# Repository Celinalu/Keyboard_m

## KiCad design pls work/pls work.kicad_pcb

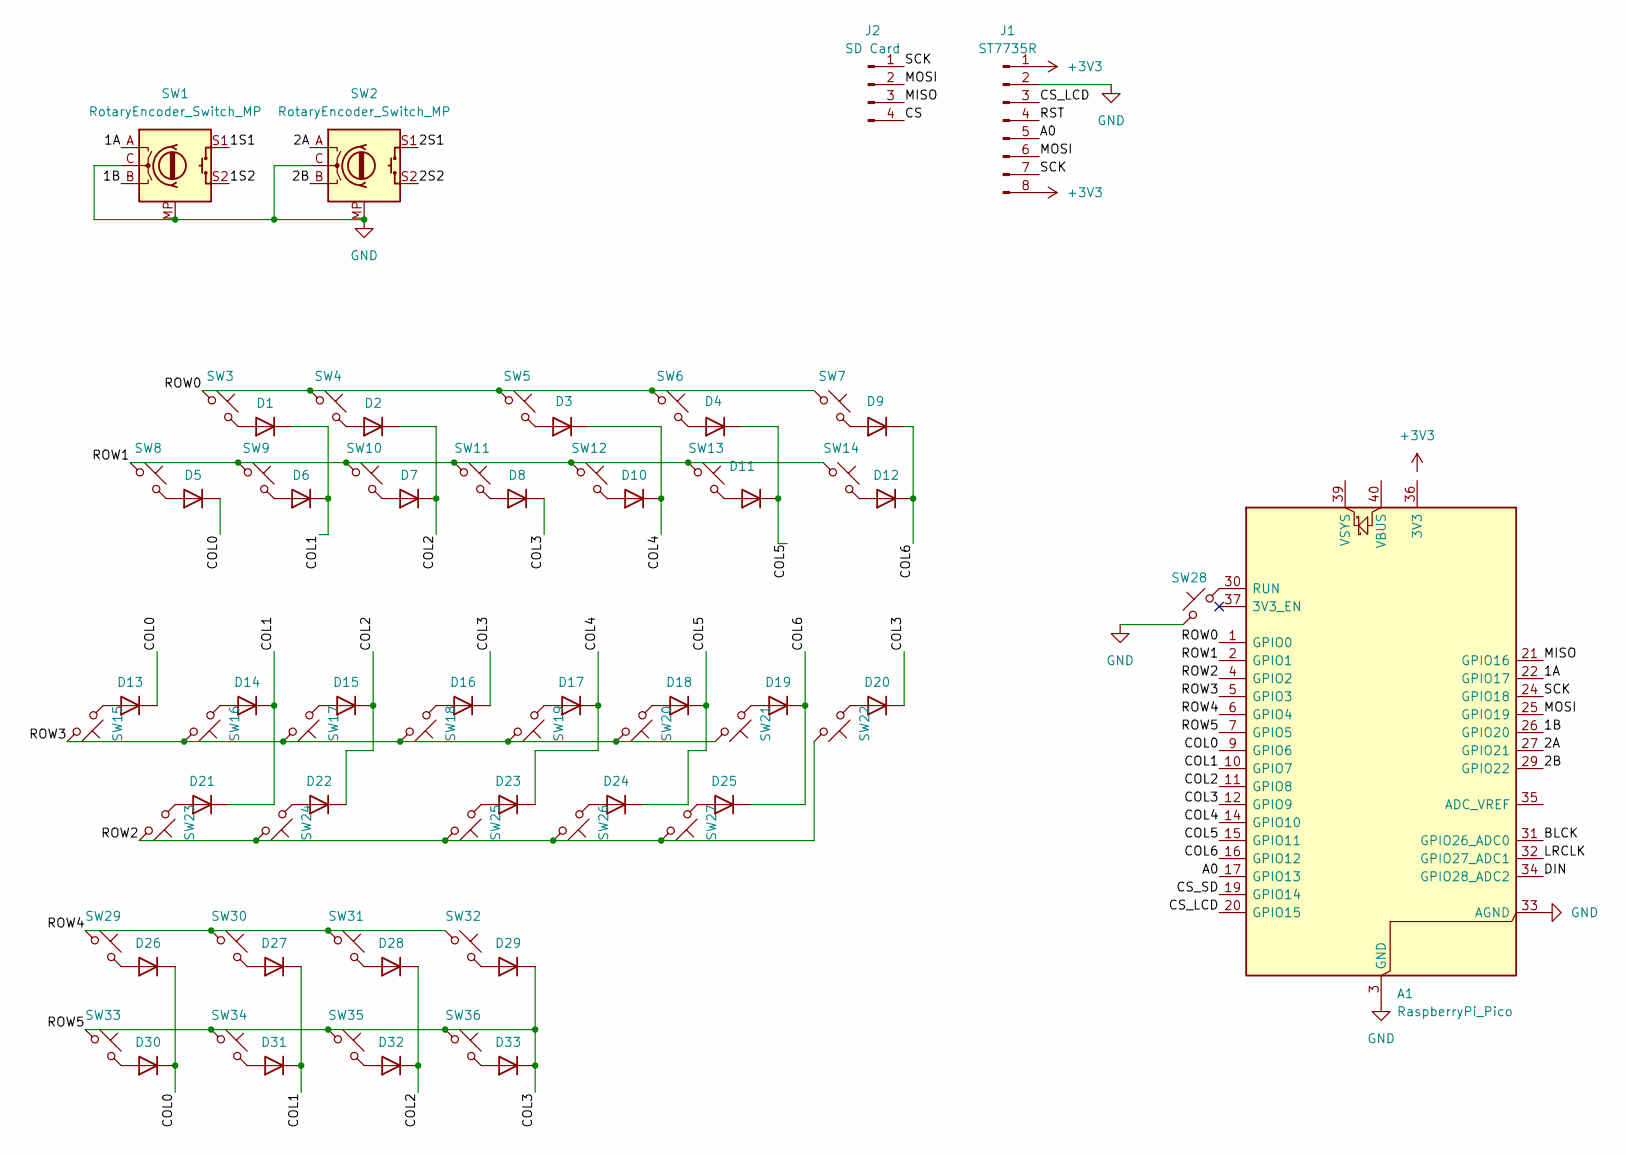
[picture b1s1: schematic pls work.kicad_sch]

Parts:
A1: RaspberryPi_Pico; RaspberryPi_Pico_Common_THT
D1, D2, D3, D4, D5, D6, D7, D8, D9, D10, D11, D12, D13, D14, D15, D16, D17, D18, D19, D20, D21, D22, D23, D24, D25, D26, D27, D28, D29, D30, D31, D32, D33: 1N4148; D_DO-35_SOD27_P7.62mm_Horizontal
J1: ST7735R; PinHeader_1x08_P1.00mm_Vertical
J2: SD Card; PinHeader_1x04_P1.00mm_Vertical
SW1, SW2: RotaryEncoder_Switch_MP; RotaryEncoder_Alps_EC11E-Switch_Vertical_H20mm_MountingHoles
SW3, SW4, SW5, SW6, SW7, SW8, SW9, SW10, SW11, SW12, SW13, SW14, SW15, SW16, SW17, SW18, SW19, SW20, SW21, SW22, SW23, SW24, SW25, SW26, SW27, SW28, SW29, SW30, SW31, SW32, SW33, SW34, SW35, SW36: SW_Push_45deg; SW_Cherry_MX_1.00u_PCB

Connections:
+3V3: J1.1, J1.8
/1A: A1.22 (GPIO17), SW1.A
/1B: A1.26 (GPIO20), SW1.B
/1S1: SW1.S1
/1S2: SW1.S2
/2A: A1.27 (GPIO21), SW2.A
/2B: A1.29 (GPIO22), SW2.B
/2S1: SW2.S1
/2S2: SW2.S2
/A0: A1.17 (GPIO13), J1.5
/BLCK: A1.31 (GPIO26_ADC0)
/COL0: A1.9 (GPIO6), D5.1 (K), D13.1 (K), D26.1 (K), D30.1 (K)
/COL1: A1.10 (GPIO7), D1.1 (K), D6.1 (K), D14.1 (K), D21.1 (K), D27.1 (K), D31.1 (K)
/COL2: A1.11 (GPIO8), D2.1 (K), D7.1 (K), D15.1 (K), D22.1 (K), D28.1 (K), D32.1 (K)
/COL3: A1.7 (GPIO5), A1.12 (GPIO9), D8.1 (K), D16.1 (K), D20.1 (K), D29.1 (K), D33.1 (K), SW33.1, SW34.1, SW35.1, SW36.1
/COL4: A1.14 (GPIO10), D3.1 (K), D10.1 (K), D17.1 (K), D23.1 (K)
/COL5: A1.15 (GPIO11), D4.1 (K), D11.1 (K), D18.1 (K), D24.1 (K)
/COL6: A1.16 (GPIO12), D9.1 (K), D12.1 (K), D19.1 (K), D25.1 (K)
/CS: J2.4
/CS_LCD: A1.20 (GPIO15), J1.3
/CS_SD: A1.19 (GPIO14)
/DIN: A1.34 (GPIO28_ADC2)
/LRCLK: A1.32 (GPIO27_ADC1)
/MISO: A1.21 (GPIO16), J2.3
/MOSI: A1.25 (GPIO19), J1.6, J2.2
/ROW0: A1.1 (GPIO0), SW3.1, SW4.1, SW5.1, SW6.1, SW7.1
/ROW1: A1.2 (GPIO1), SW8.1, SW9.1, SW10.1, SW11.1, SW12.1, SW13.1, SW14.1
/ROW2: A1.4 (GPIO2), SW22.2, SW23.2, SW24.2, SW25.2, SW26.2, SW27.2
/ROW3: A1.5 (GPIO3), SW15.2, SW16.2, SW17.2, SW18.2, SW19.2, SW20.2, SW21.2
/ROW4: A1.6 (GPIO4), SW29.1, SW30.1, SW31.1, SW32.1
/RST: J1.4
/SCK: A1.24 (GPIO18), J1.7, J2.1
GND: A1.3 (GND), A1.8 (GND), A1.13 (GND), A1.18 (GND), A1.23 (GND), A1.28 (GND), A1.33 (AGND), A1.38 (GND), J1.2, SW1.C, SW1.MP, SW2.C, SW2.MP, SW28.1
unnamed: A1.30 (RUN), SW28.2
unnamed: D1.2 (A), SW3.2
unnamed: D2.2 (A), SW4.2
unnamed: D3.2 (A), SW5.2
unnamed: D4.2 (A), SW6.2
unnamed: D5.2 (A), SW8.2
unnamed: D6.2 (A), SW9.2
unnamed: D7.2 (A), SW10.2
unnamed: D8.2 (A), SW11.2
unnamed: D9.2 (A), SW7.2
unnamed: D10.2 (A), SW12.2
unnamed: D11.2 (A), SW13.2
unnamed: D12.2 (A), SW14.2
unnamed: D13.2 (A), SW15.1
unnamed: D14.2 (A), SW16.1
unnamed: D15.2 (A), SW17.1
unnamed: D16.2 (A), SW18.1
unnamed: D17.2 (A), SW19.1
unnamed: D18.2 (A), SW20.1
unnamed: D19.2 (A), SW21.1
unnamed: D20.2 (A), SW22.1
unnamed: D21.2 (A), SW23.1
unnamed: D22.2 (A), SW24.1
unnamed: D23.2 (A), SW25.1
unnamed: D24.2 (A), SW26.1
unnamed: D25.2 (A), SW27.1
unnamed: D26.2 (A), SW29.2
unnamed: D27.2 (A), SW30.2
unnamed: D28.2 (A), SW31.2
unnamed: D29.2 (A), SW32.2
unnamed: D30.2 (A), SW33.2
unnamed: D31.2 (A), SW34.2
unnamed: D32.2 (A), SW35.2
unnamed: D33.2 (A), SW36.2

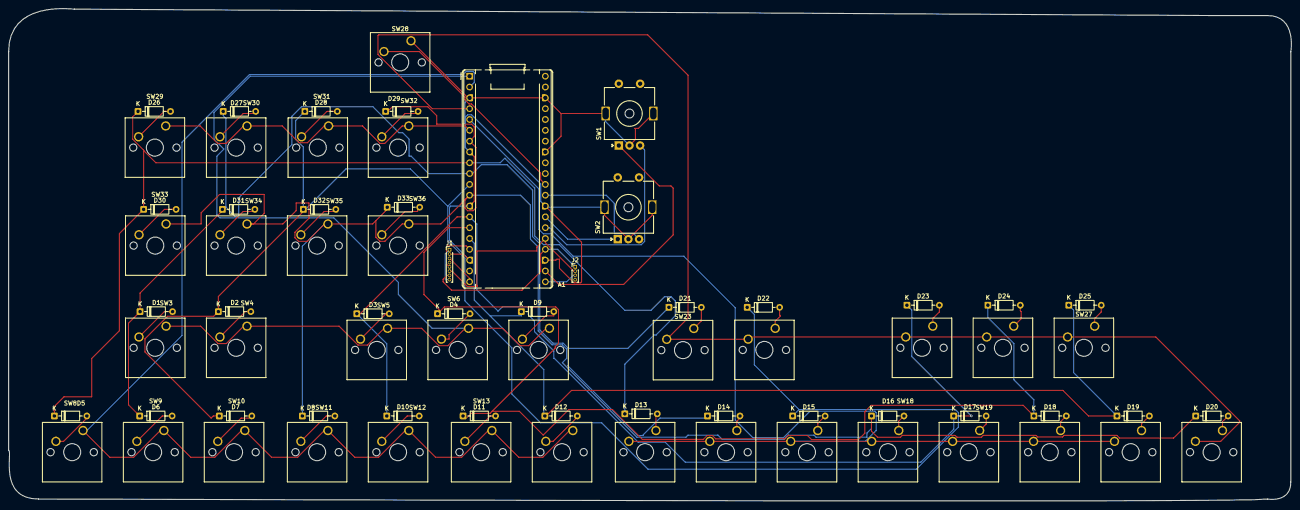
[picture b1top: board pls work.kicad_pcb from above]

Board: 2 copper layers, 301.1 x 115.6 mm, 72 parts (0 on the bottom side), 57 nets.

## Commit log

2026-04-05 doing schematic work!!!
    going ok i think..
2026-04-05 doing schematic work
    idk what happened to the last commit
2026-04-05 still working on schematic stuff
    still got a bunch to do... idk im doing it right
2026-04-06 finished schematic (hopefully), did footprints, now doing pcb
    struggling not too bad rn tho
2026-04-06 WIRING
    soooo much wiring
2026-04-06 wiring is NOT working
    restarting now trying to come up with a better plan
2026-04-06 still wiring...
    these wires r killing meee
2026-04-06 done the wiring
    but got like 140 warnings...
2026-04-11 was just working on clearing all the errors
    Why is all my work not showing up???
2026-04-11 ok now my error fixing work is showing up
2026-04-11 fixed most of my issues
    just a few spacing problems that I will have to figure out later
